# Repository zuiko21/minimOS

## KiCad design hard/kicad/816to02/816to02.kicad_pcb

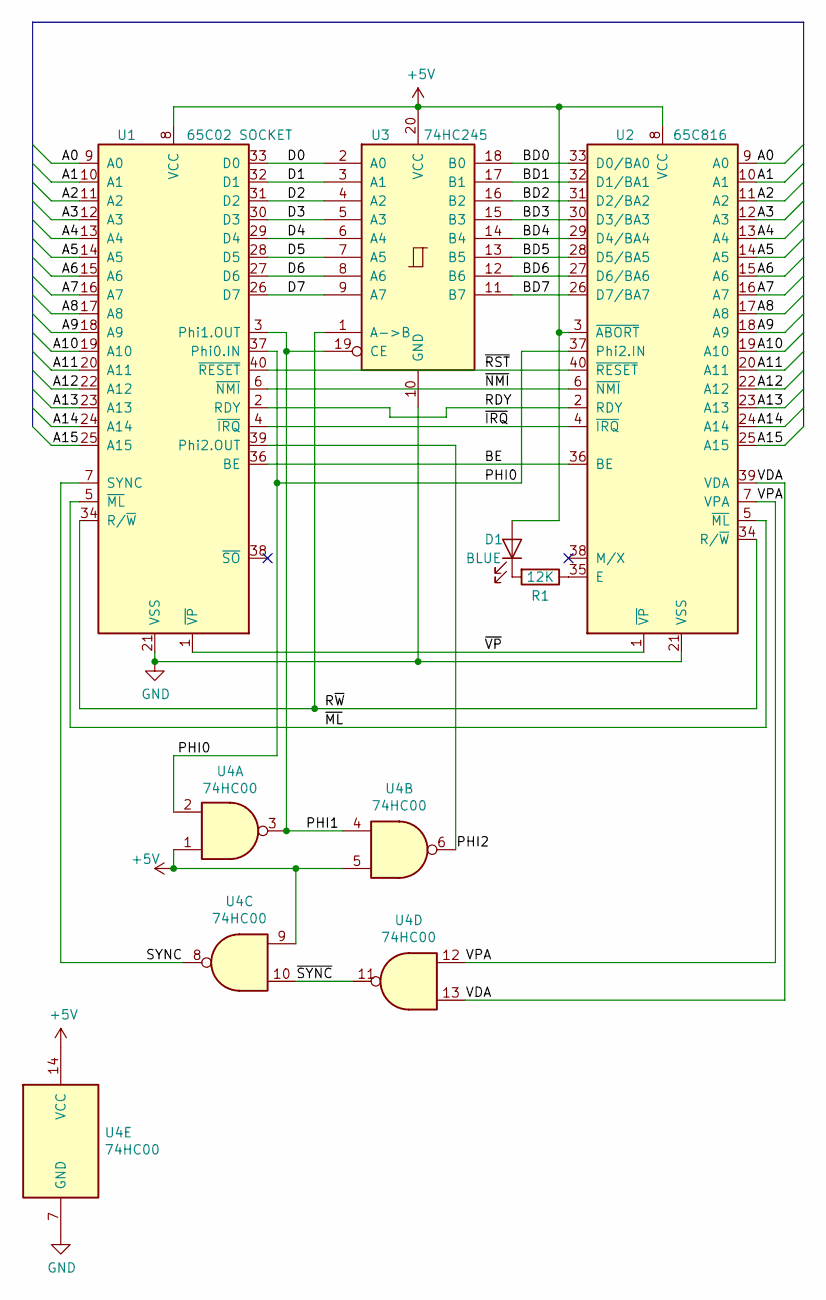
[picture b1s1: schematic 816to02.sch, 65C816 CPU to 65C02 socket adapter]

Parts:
D1: BLUE; LED_D3.0mm_Horizontal_O6.35mm_Z2.0mm
R1: 12K; R_0805_2012Metric_Pad1.15x1.40mm_HandSolder
U1: 65C02 SOCKET; DIP-40_W15.24mm_Socket
U2: 65C816; DIP-40_W15.24mm_Socket
U3: 74HC245; DIP-20_W7.62mm
U4: 74HC00; DIP-14_W7.62mm

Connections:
+5V: D1.2 (A), U1.8 (VCC), U2.3 (~ABORT), U2.8 (VCC), U3.20 (VCC), U4.1, U4.5, U4.9, U4.14 (VCC)
/A0: U1.9 (A0), U2.9 (A0)
/A1: U1.10 (A1), U2.10 (A1)
/A2: U1.11 (A2), U2.11 (A2)
/A3: U1.12 (A3), U2.12 (A3)
/A4: U1.13 (A4), U2.13 (A4)
/A5: U1.14 (A5), U2.14 (A5)
/A6: U1.15 (A6), U2.15 (A6)
/A7: U1.16 (A7), U2.16 (A7)
/A8: U1.17 (A8), U2.17 (A8)
/A9: U1.18 (A9), U2.18 (A9)
/A10: U1.19 (A10), U2.19 (A10)
/A11: U1.20 (A11), U2.20 (A11)
/A12: U1.22 (A12), U2.22 (A12)
/A13: U1.23 (A13), U2.23 (A13)
/A14: U1.24 (A14), U2.24 (A14)
/A15: U1.25 (A15), U2.25 (A15)
/BD0: U2.33 (D0/BA0), U3.18 (B0)
/BD1: U2.32 (D1/BA1), U3.17 (B1)
/BD2: U2.31 (D2/BA2), U3.16 (B2)
/BD3: U2.30 (D3/BA3), U3.15 (B3)
/BD4: U2.29 (D4/BA4), U3.14 (B4)
/BD5: U2.28 (D5/BA5), U3.13 (B5)
/BD6: U2.27 (D6/BA6), U3.12 (B6)
/BD7: U2.26 (D7/BA7), U3.11 (B7)
/BE: U1.36 (BE), U2.36 (BE)
/D0: U1.33 (D0), U3.2 (A0)
/D1: U1.32 (D1), U3.3 (A1)
/D2: U1.31 (D2), U3.4 (A2)
/D3: U1.30 (D3), U3.5 (A3)
/D4: U1.29 (D4), U3.6 (A4)
/D5: U1.28 (D5), U3.7 (A5)
/D6: U1.27 (D6), U3.8 (A6)
/D7: U1.26 (D7), U3.9 (A7)
/PHI0: U1.37 (Phi0.IN), U2.37 (Phi2.IN), U4.2
/PHI1: U1.3 (Phi1.OUT), U3.19 (CE), U4.3, U4.4
/PHI2: U1.39 (Phi2.OUT), U4.6
/RDY: U1.2 (RDY), U2.2 (RDY)
/R~W: U1.34 (R/~W), U2.34 (R/~W), U3.1 (A->B)
/SYNC: U1.7 (SYNC), U4.8
/VDA: U2.39 (VDA), U4.13
/VPA: U2.7 (VPA), U4.12
/~IRQ: U1.4 (~IRQ), U2.4 (~IRQ)
/~ML: U1.5 (~ML), U2.5 (~ML)
/~NMI: U1.6 (~NMI), U2.6 (~NMI)
/~RST: U1.40 (~RESET), U2.40 (~RESET)
/~SYNC: U4.10, U4.11
/~VP: U1.1 (~VP), U2.1 (~VP)
GND: U1.21 (VSS), U2.21 (VSS), U3.10 (GND), U4.7 (GND)
unnamed: D1.1 (K), R1.2
unnamed: R1.1, U2.35 (E)

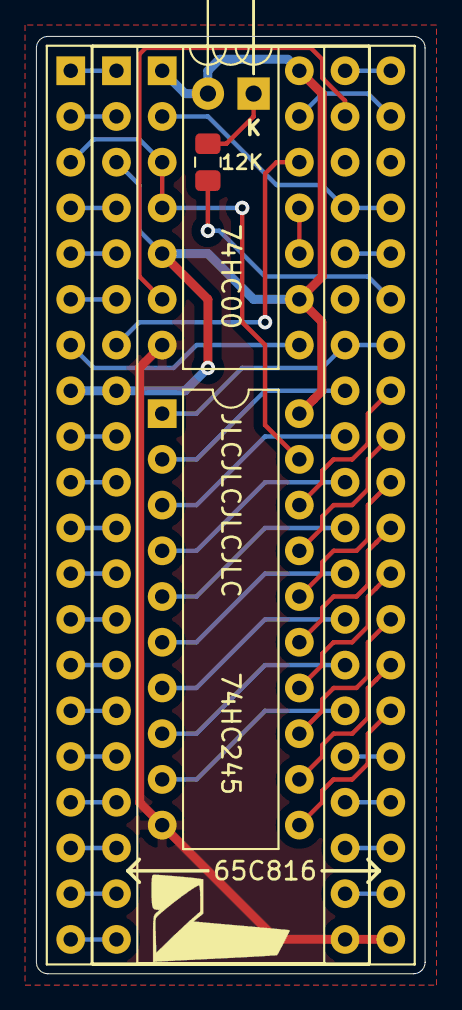
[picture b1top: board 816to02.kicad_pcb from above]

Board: 2 copper layers, 21.6 x 52.1 mm, 6 parts (0 on the bottom side), 51 nets.

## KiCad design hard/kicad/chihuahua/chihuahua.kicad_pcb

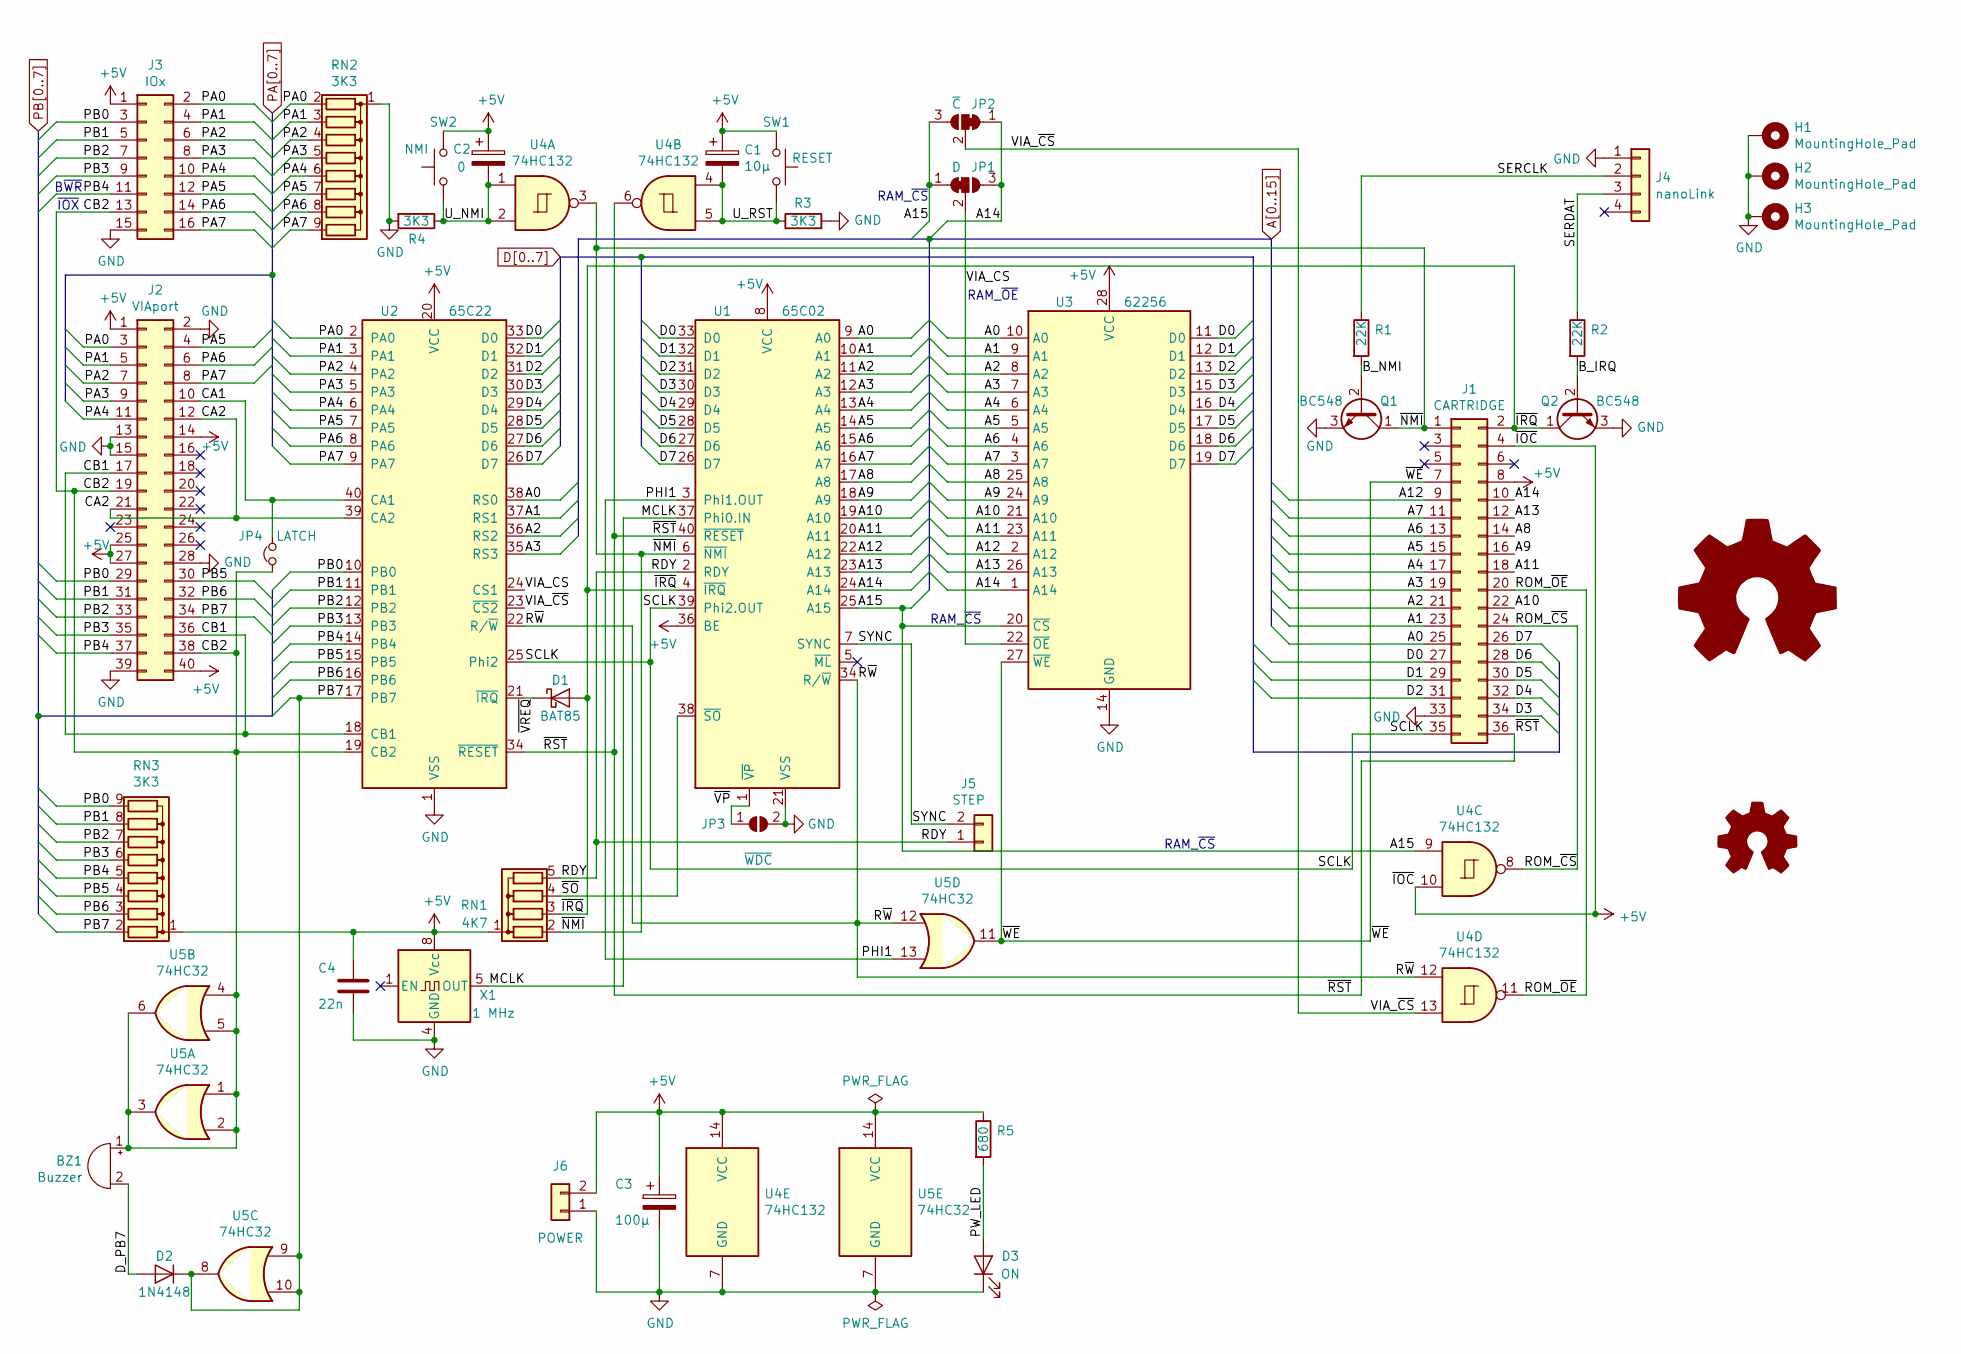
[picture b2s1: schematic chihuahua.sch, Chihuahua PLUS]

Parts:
BZ1: Buzzer; Buzzer_12x9.5RM7.6
C1: 10µ; CP_Radial_D4.0mm_P1.50mm
C2: 0; CP_Radial_D4.0mm_P1.50mm
C3: 100µ; CP_Radial_D4.0mm_P1.50mm
C4: 22n; C_Rect_L7.2mm_W2.5mm_P5.00mm_FKS2_FKP2_MKS2_MKP2
D1: BAT85; D_DO-35_SOD27_P2.54mm_Vertical_KathodeUp
D2: 1N4148; D_DO-35_SOD27_P2.54mm_Vertical_AnodeUp
D3: ON; LED_D3.0mm
H1, H2, H3: MountingHole_Pad; MountingHole_3.2mm_M3_DIN965_Pad
J1: CARTRIDGE; PinSocket_2x18_EDGE
J2: VIAport; IDC-Header_2x20_P2.54mm_Vertical
J3: IOx; IDC-Header_2x08_P2.54mm_Vertical
J4: nanoLink; PinHeader_1x04_P2.54mm_Vertical
J5: STEP; PinHeader_1x02_P2.54mm_Vertical
J6: POWER; JST_EH_S2B-EH_1x02_P2.50mm_Horizontal
JP1: D; SolderJumper-3_P1.3mm_Bridged12_RoundedPad1.0x1.5mm
JP2: ~C; SolderJumper-3_P1.3mm_Bridged12_RoundedPad1.0x1.5mm
JP3: ~WDC; SolderJumper-2_P1.3mm_Open_RoundedPad1.0x1.5mm
JP4: LATCH; PinHeader_1x02_P2.54mm_Vertical
LOGO1: Logo_Open_Hardware_Large; OSHW-Symbol_8.9x8mm_SilkScreen
LOGO2: Logo_Open_Hardware_Small; jaqueria
Q1, Q2: BC548; TO-92_Inline
R1, R2: 22K; R_Axial_DIN0207_L6.3mm_D2.5mm_P2.54mm_Vertical
R3, R4: 3K3; R_Axial_DIN0207_L6.3mm_D2.5mm_P2.54mm_Vertical
R5: 680; R_Axial_DIN0207_L6.3mm_D2.5mm_P2.54mm_Vertical
RN1: 4K7; R_Array_SIP5
RN2, RN3: 3K3; R_Array_SIP9
SW1: RESET; SW_PUSH_6mm
SW2: NMI; SW_PUSH_6mm
U1: 65C02; DIP-40_W15.24mm_Socket
U2: 65C22; DIP-40_W15.24mm_Socket
U3: 62256; DIP-28_W15.24mm_Socket
U4: 74HC132; DIP-14_W7.62mm_Socket
U5: 74HC32; DIP-14_W7.62mm_Socket
X1: 1 MHz; Oscillator_DIP-8

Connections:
+5V: C1.1, C2.1, C3.1, C4.1, J1.4, J1.8, J2.1, J2.14, J2.25, J2.27, J2.40, J3.1, J6.2, R5.1, RN1.1 (common), RN3.1 (common), SW1.2, SW2.2, U1.8 (VCC), U1.36 (BE), U2.20 (VCC), U3.28 (VCC), U4.10, U4.14 (VCC), U5.14 (VCC), X1.8 (Vcc)
/B_IRQ: Q2.2 (B), R2.2
/B_NMI: Q1.2 (B), R1.2
/CA1: J2.10, JP4.1, U2.40 (CA1)
/CA2: J2.12, J2.21, U2.39 (CA2)
/CB1: J2.17, J2.36, U2.18 (CB1)
/CB2: BZ1.1 (-), J2.19, J2.38, J3.13, JP4.2, U2.19 (CB2), U5.1, U5.2, U5.3, U5.4, U5.5, U5.6
/D_PB7: BZ1.2 (+), D2.2 (A)
/MCLK: U1.37 (Phi0.IN), X1.5 (OUT)
/PHI1: U1.3 (Phi1.OUT), U5.13
/PW_LED: D3.2 (A), R5.2
/RDY: J5.1, RN1.5 (R4), U1.2 (RDY)
/ROM_~CS: J1.24, U4.8
/ROM_~OE: J1.20, U4.11
/R~W: U1.34 (R/~W), U2.22 (R/~W), U4.12, U5.12
/SCLK: J1.35, U1.39 (Phi2.OUT), U2.25 (Phi2)
/SERCLK: J4.2, R1.1
/SERDAT: J4.3, R2.1
/SYNC: J5.2, U1.7 (SYNC)
/U_NMI: C2.2, R4.1, SW2.1, U4.1, U4.2
/U_RST: C1.2, R3.1, SW1.1, U4.4, U4.5
/VIA_CS: JP1.2 (C), U2.24 (CS1), U3.22 (~OE~)
/VIA_~CS: JP2.2 (C), U2.23 (~CS2), U4.13
/~IRQ: D1.2 (A), J1.2, Q2.1 (C), RN1.3 (R2), U1.4 (~IRQ)
/~NMI: J1.1, Q1.1 (C), RN1.2 (R1), U1.6 (~NMI), U4.3
/~RST: J1.36, U1.40 (~RESET), U2.34 (~RESET), U4.6
/~SO: RN1.4 (R3), U1.38 (~SO)
/~VP: JP3.1 (A), U1.1 (~VP)
/~VREQ: D1.1 (K), U2.21 (~IRQ)
/~WE: J1.7, U3.27 (~WE~), U5.11
A0: J1.25, U1.9 (A0), U2.38 (RS0), U3.10 (A0)
A1: J1.23, U1.10 (A1), U2.37 (RS1), U3.9 (A1)
A2: J1.21, U1.11 (A2), U2.36 (RS2), U3.8 (A2)
A3: J1.19, U1.12 (A3), U2.35 (RS3), U3.7 (A3)
A4: J1.17, U1.13 (A4), U3.6 (A4)
A5: J1.15, U1.14 (A5), U3.5 (A5)
A6: J1.13, U1.15 (A6), U3.4 (A6)
A7: J1.11, U1.16 (A7), U3.3 (A7)
A8: J1.14, U1.17 (A8), U3.25 (A8)
A9: J1.16, U1.18 (A9), U3.24 (A9)
A10: J1.22, U1.19 (A10), U3.21 (A10)
A11: J1.18, U1.20 (A11), U3.23 (A11)
A12: J1.9, U1.22 (A12), U3.2 (A12)
A13: J1.12, U1.23 (A13), U3.26 (A13)
A14: J1.10, JP1.3 (B), JP2.1 (A), U1.24 (A14), U3.1 (A14)
A15: JP1.1 (A), JP2.3 (B), U1.25 (A15), U3.20 (~CS), U4.9
D0: J1.27, U1.33 (D0), U2.33 (D0), U3.11 (D0)
D1: J1.29, U1.32 (D1), U2.32 (D1), U3.12 (D1)
D2: J1.31, U1.31 (D2), U2.31 (D2), U3.13 (D2)
D3: J1.34, U1.30 (D3), U2.30 (D3), U3.15 (D3)
D4: J1.32, U1.29 (D4), U2.29 (D4), U3.16 (D4)
D5: J1.30, U1.28 (D5), U2.28 (D5), U3.17 (D5)
D6: J1.28, U1.27 (D6), U2.27 (D6), U3.18 (D6)
D7: J1.26, U1.26 (D7), U2.26 (D7), U3.19 (D7)
GND: C3.2, C4.2, D3.1 (K), H1.1, H2.1, H3.1, J1.33, J2.2, J2.13, J2.15, J2.28, J2.39, J3.15, J4.1, J6.1, JP3.2 (B), Q1.3 (E), Q2.3 (E), R3.2, R4.2, RN2.1 (common), U1.21 (VSS), U2.1 (VSS), U3.14 (GND), U4.7 (GND), U5.7 (GND), X1.4 (GND)
PA0: J2.3, J3.2, RN2.2 (R1), U2.2 (PA0)
PA1: J2.5, J3.4, RN2.3 (R2), U2.3 (PA1)
PA2: J2.7, J3.6, RN2.4 (R3), U2.4 (PA2)
PA3: J2.9, J3.8, RN2.5 (R4), U2.5 (PA3)
PA4: J2.11, J3.10, RN2.6 (R5), U2.6 (PA4)
PA5: J2.4, J3.12, RN2.7 (R6), U2.7 (PA5)
PA6: J2.6, J3.14, RN2.8 (R7), U2.8 (PA6)
PA7: J2.8, J3.16, RN2.9 (R8), U2.9 (PA7)
PB0: J2.29, J3.3, RN3.9 (R8), U2.10 (PB0)
PB1: J2.31, J3.5, RN3.8 (R7), U2.11 (PB1)
PB2: J2.33, J3.7, RN3.7 (R6), U2.12 (PB2)
PB3: J2.35, J3.9, RN3.6 (R5), U2.13 (PB3)
PB4: J2.37, J3.11, RN3.5 (R4), U2.14 (PB4)
PB5: J2.30, RN3.4 (R3), U2.15 (PB5)
PB6: J2.32, RN3.3 (R2), U2.16 (PB6)
PB7: D2.1 (K), J2.34, RN3.2 (R1), U2.17 (PB7), U5.8, U5.9, U5.10

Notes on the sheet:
B~WR
~IOX
RAM_~CS
RAM_~OE

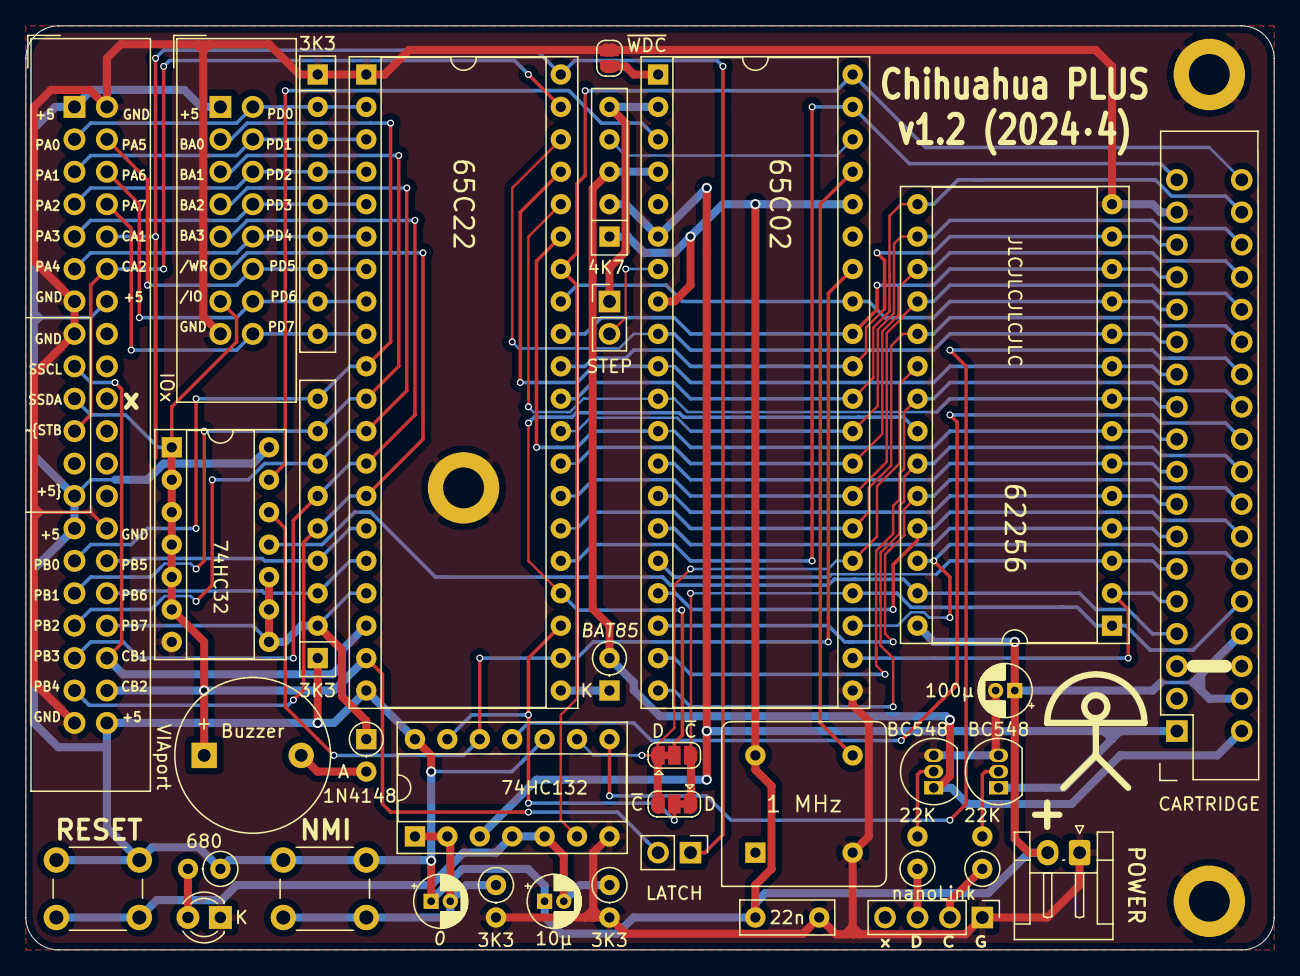
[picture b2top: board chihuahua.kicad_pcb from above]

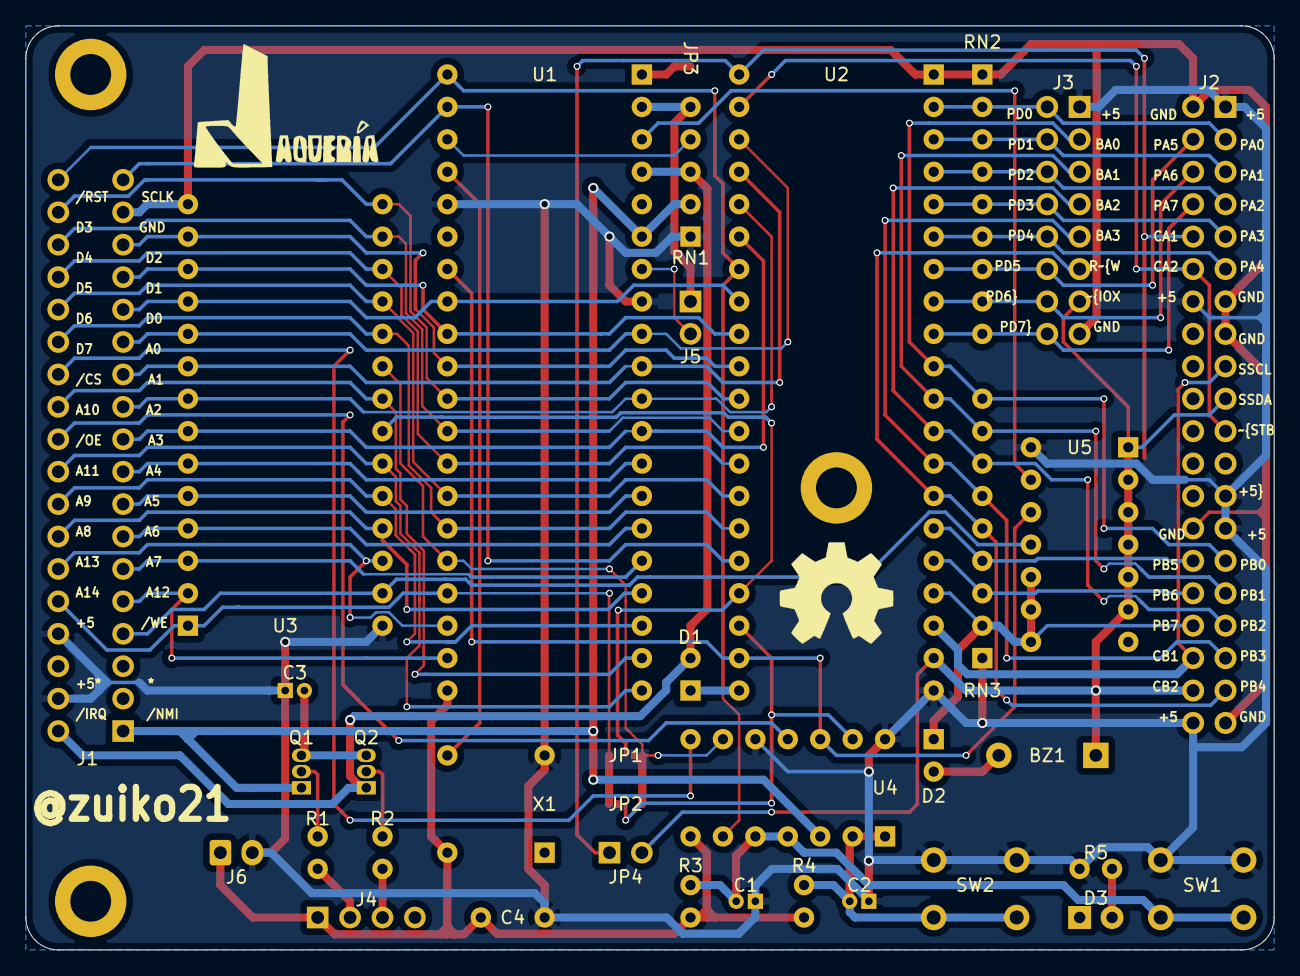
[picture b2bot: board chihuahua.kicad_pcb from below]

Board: 2 copper layers, 97.8 x 72.4 mm, 41 parts (2 on the bottom side), 71 nets.

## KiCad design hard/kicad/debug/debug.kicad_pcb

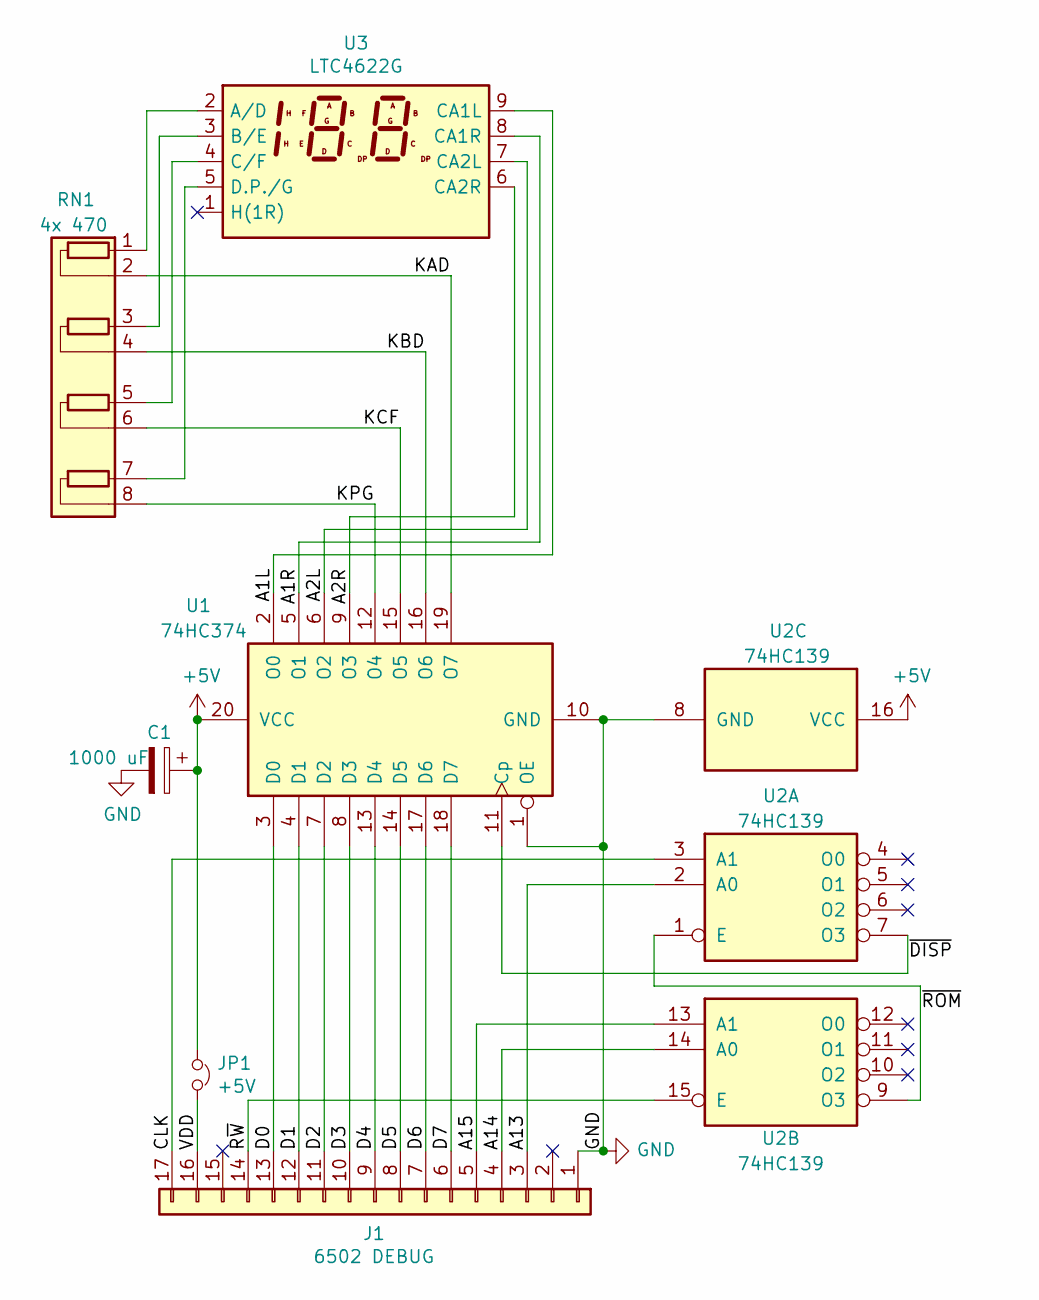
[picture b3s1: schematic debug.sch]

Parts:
C1: 1000 uF; CP_Radial_D10.0mm_P5.00mm
J1: 6502 DEBUG; PinHeader_1x17_P2.54mm_Horizontal
JP1: +5V; PinHeader_1x02_P2.54mm_Vertical
RN1: 4x 470; R_Array_SIP8
U1: 74HC374; DIP-20_W7.62mm_Socket
U2: 74HC139; DIP-16_W7.62mm_Socket
U3: LTC4622G; PinSocket_1x09_P2.54mm_Vertical

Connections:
+5V: C1.1, JP1.1, U1.20 (VCC), U2.16 (VCC)
/A1L: U1.2 (O0), U3.9 (CA1L)
/A1R: U1.5 (O1), U3.8 (CA1R)
/A2L: U1.6 (O2), U3.7 (CA2L)
/A2R: U1.9 (O3), U3.6 (CA2R)
/A13: J1.3, U2.2 (A0)
/A14: J1.4, U2.14 (A0)
/A15: J1.5, U2.13 (A1)
/CLK: J1.17, U2.3 (A1)
/D0: J1.13, U1.3 (D0)
/D1: J1.12, U1.4 (D1)
/D2: J1.11, U1.7 (D2)
/D3: J1.10, U1.8 (D3)
/D4: J1.9, U1.13 (D4)
/D5: J1.8, U1.14 (D5)
/D6: J1.7, U1.17 (D6)
/D7: J1.6, U1.18 (D7)
/KAD: RN1.2 (R1.2), U1.19 (O7)
/KBD: RN1.4 (R2.2), U1.16 (O6)
/KCF: RN1.6 (R3.2), U1.15 (O5)
/KPG: RN1.8 (R4.2), U1.12 (O4)
/R~W: J1.14, U2.15 (E)
/VDD: J1.16, JP1.2
/~DISP: U1.11 (Cp), U2.7 (O3)
/~ROM: U2.1 (E), U2.9 (O3)
GND: C1.2, J1.1, U1.1 (OE), U1.10 (GND), U2.8 (GND)
unnamed: RN1.1 (R1.1), U3.2 (A/D)
unnamed: RN1.3 (R2.1), U3.3 (B/E)
unnamed: RN1.5 (R3.1), U3.4 (C/F)
unnamed: RN1.7 (R4.1), U3.5 (D.P./G)

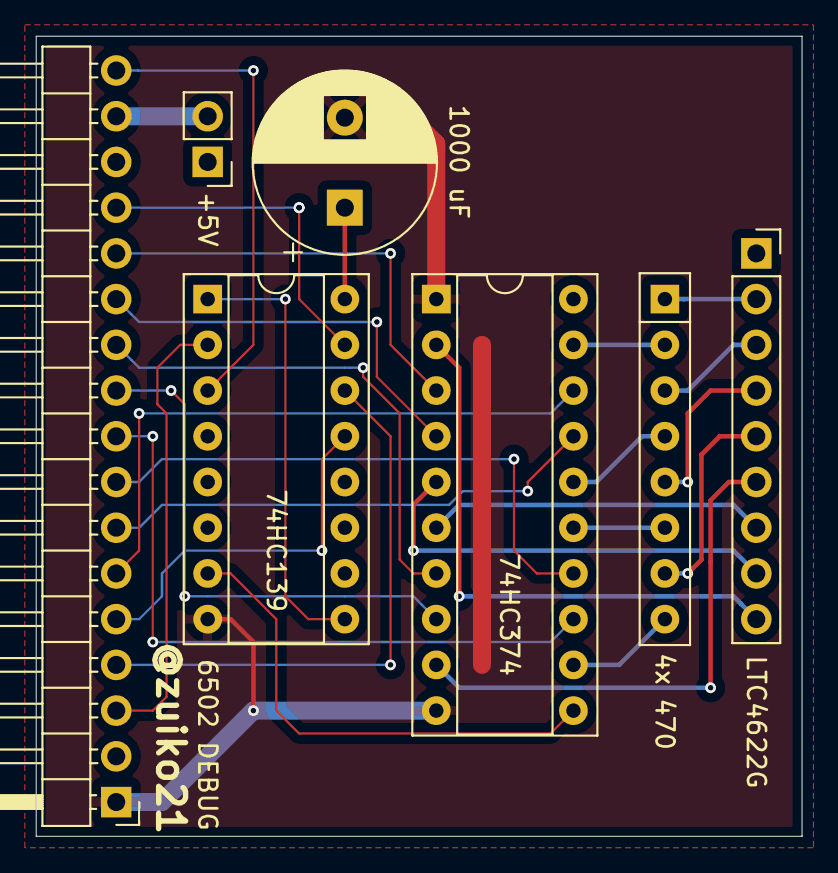
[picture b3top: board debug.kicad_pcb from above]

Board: 2 copper layers, 42.5 x 44.5 mm, 7 parts (0 on the bottom side), 30 nets.

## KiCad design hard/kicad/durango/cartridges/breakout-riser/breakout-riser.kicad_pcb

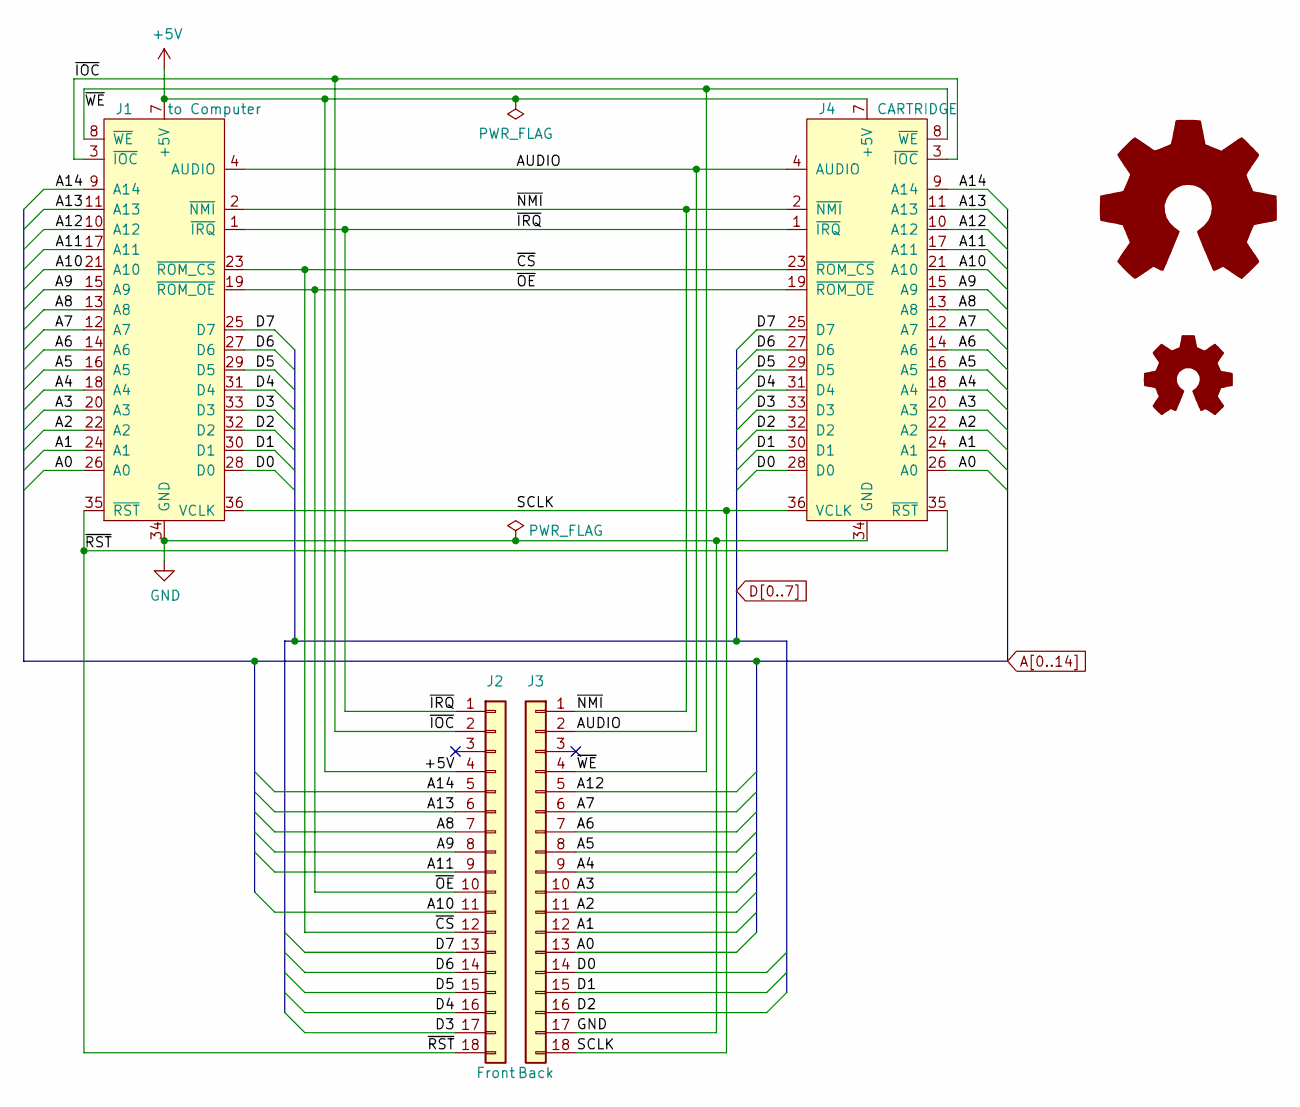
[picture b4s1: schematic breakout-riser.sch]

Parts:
J1: to Computer; Durango_ROM
J2: Front; PinHeader_1x18_P2.54mm_Vertical
J3: Back; PinHeader_1x18_P2.54mm_Vertical
J4: CARTRIDGE; PinSocket_2x18_EDGE
LOGO1: Logo_Open_Hardware_Large; jaqueria
LOGO2: Logo_Open_Hardware_Small; OSHW-Logo2_9.8x8mm_SilkScreen

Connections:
+5V: J1.7 (+5V), J2.4, J4.7 (+5V)
/AUDIO: J1.4 (AUDIO), J3.2, J4.4 (AUDIO)
/SCLK: J1.36 (VCLK), J3.18, J4.36 (VCLK)
/~CS: J1.23 (~ROM_CS), J2.12, J4.23 (~ROM_CS)
/~IOC: J1.3 (~IOC), J2.2, J4.3 (~IOC)
/~IRQ: J1.1 (~IRQ), J2.1, J4.1 (~IRQ)
/~NMI: J1.2 (~NMI), J3.1, J4.2 (~NMI)
/~OE: J1.19 (~ROM_OE), J2.10, J4.19 (~ROM_OE)
/~RST: J1.35 (~RST), J2.18, J4.35 (~RST)
/~WE: J1.8 (~WE), J3.4, J4.8 (~WE)
A0: J1.26 (A0), J3.13, J4.26 (A0)
A1: J1.24 (A1), J3.12, J4.24 (A1)
A2: J1.22 (A2), J3.11, J4.22 (A2)
A3: J1.20 (A3), J3.10, J4.20 (A3)
A4: J1.18 (A4), J3.9, J4.18 (A4)
A5: J1.16 (A5), J3.8, J4.16 (A5)
A6: J1.14 (A6), J3.7, J4.14 (A6)
A7: J1.12 (A7), J3.6, J4.12 (A7)
A8: J1.13 (A8), J2.7, J4.13 (A8)
A9: J1.15 (A9), J2.8, J4.15 (A9)
A10: J1.21 (A10), J2.11, J4.21 (A10)
A11: J1.17 (A11), J2.9, J4.17 (A11)
A12: J1.10 (A12), J3.5, J4.10 (A12)
A13: J1.11 (A13), J2.6, J4.11 (A13)
A14: J1.9 (A14), J2.5, J4.9 (A14)
D0: J1.28 (D0), J3.14, J4.28 (D0)
D1: J1.30 (D1), J3.15, J4.30 (D1)
D2: J1.32 (D2), J3.16, J4.32 (D2)
D3: J1.33 (D3), J2.17, J4.33 (D3)
D4: J1.31 (D4), J2.16, J4.31 (D4)
D5: J1.29 (D5), J2.15, J4.29 (D5)
D6: J1.27 (D6), J2.14, J4.27 (D6)
D7: J1.25 (D7), J2.13, J4.25 (D7)
GND: J1.34 (GND), J3.17, J4.34 (GND)

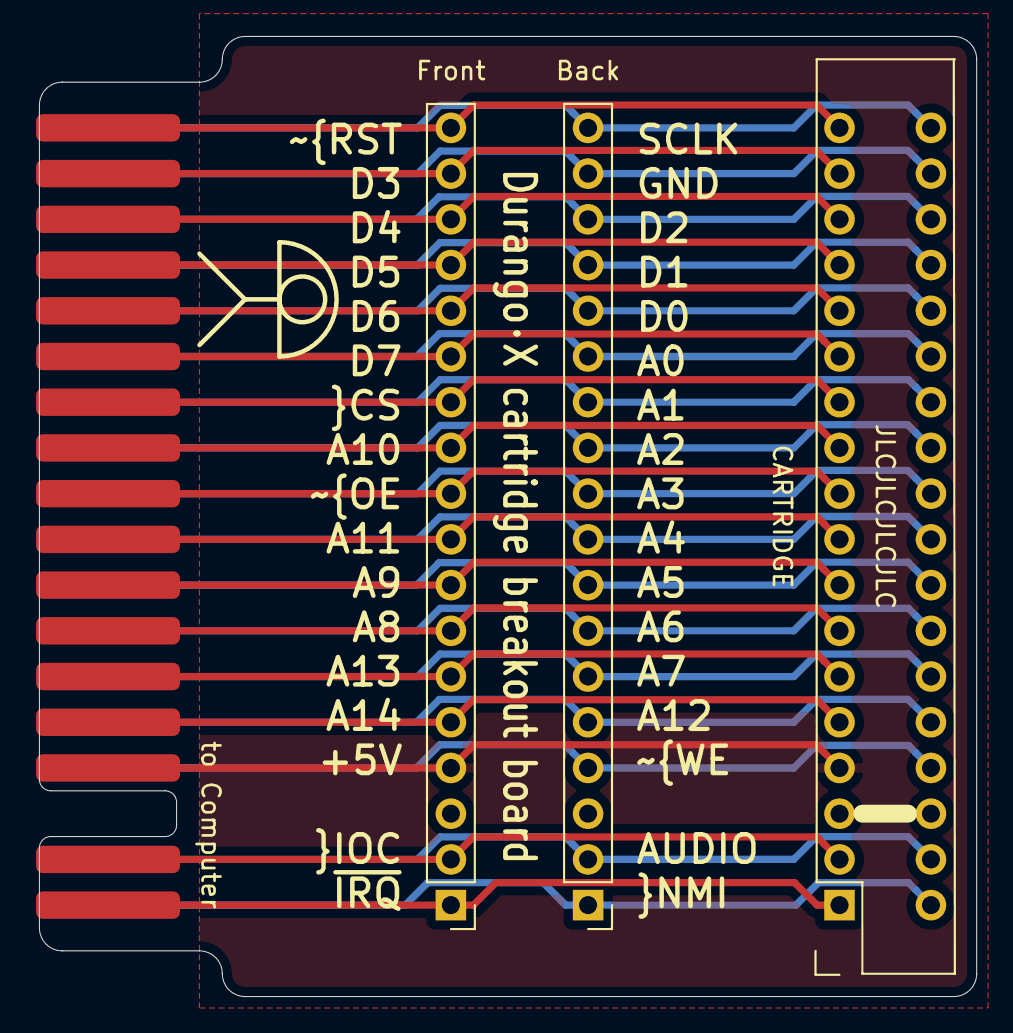
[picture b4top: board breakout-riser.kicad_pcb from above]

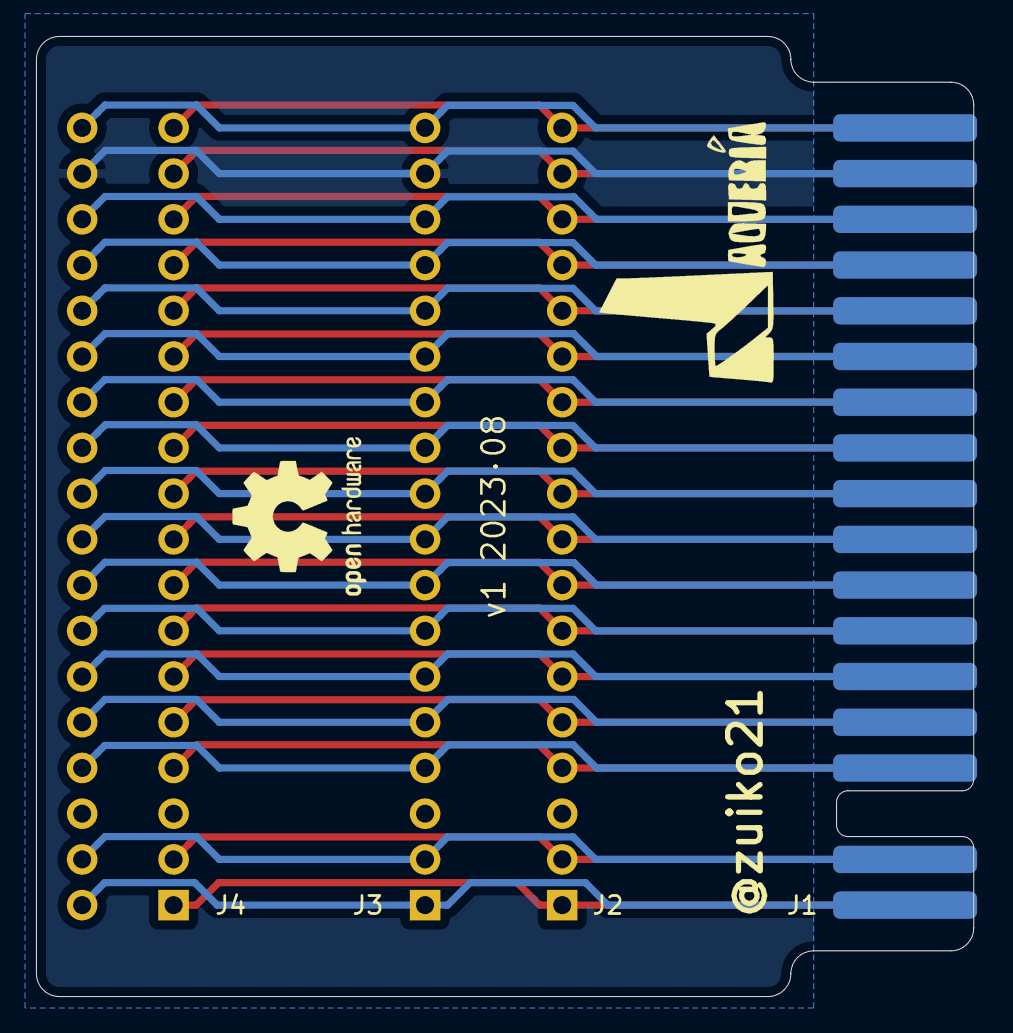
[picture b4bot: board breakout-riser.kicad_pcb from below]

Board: 2 copper layers, 52.1 x 53.3 mm, 6 parts (2 on the bottom side), 34 nets.

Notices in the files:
hard/kicad/chihuahua/chihuahua.sch:
(c) 2012-2023 Carlos J. Santisteban
